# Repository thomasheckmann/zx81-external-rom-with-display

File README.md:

# zx81-external-rom-with-display
ZX81 External ROM interface with partial display logic. The aim of this interface is to be able to run ZX81 ROMS with alternative character set, as found in different Forth ROMS and the ASZMIC rom, without having the need to open up your ZX81 and replace the internal ROM.

Partial display logic only, as this is what's available at the extension bus.

# version 1.0
Board populated with all components. Works great and can even downgrade your ZX81 to a ZX80 :-)

With this interface it is now possible to run ROMs such as the ZX.ASZMIC, Skyware Forth and even the ZX80 ROM.

PLEASE NOTE: The display with this interface will make the ZX81 run as in FAST mode, since there is for now no way to implement the SLOW mode display externally. And one of the main goal is to avoid modifying your existing ZX81.

BOM for v1.0:
- [ ] M28C64 EEPROM (8K eeprom)
- [ ] 74LS157 x 3
- [ ] 74LS193
- [ ] 74LS374
- [ ] Diode 1N4148 x 3
- [ ] Resistor 10K
- [ ] 100nF Ceramic Capacitor x 6

## Planned for v1.1
Only some small changes are planned for v1.1 - mostly the NMI generator fix. When running the ZX80 ROM the NMI generator is not turned off, which means the initial state of the generator is unpredictible. For this reason running the ZX80 not always turns out to work, a few on/off should make it work. A simple fix is to make sure the NMI generator is turned off, by using a few resistors.

Will change the diode from 1N4148 to BAT85, as recommended for this type of usage.

Replace IC socket with ZIF Test socket, as it turns out that I'm swapping out EEPROMs based on needs and usage.

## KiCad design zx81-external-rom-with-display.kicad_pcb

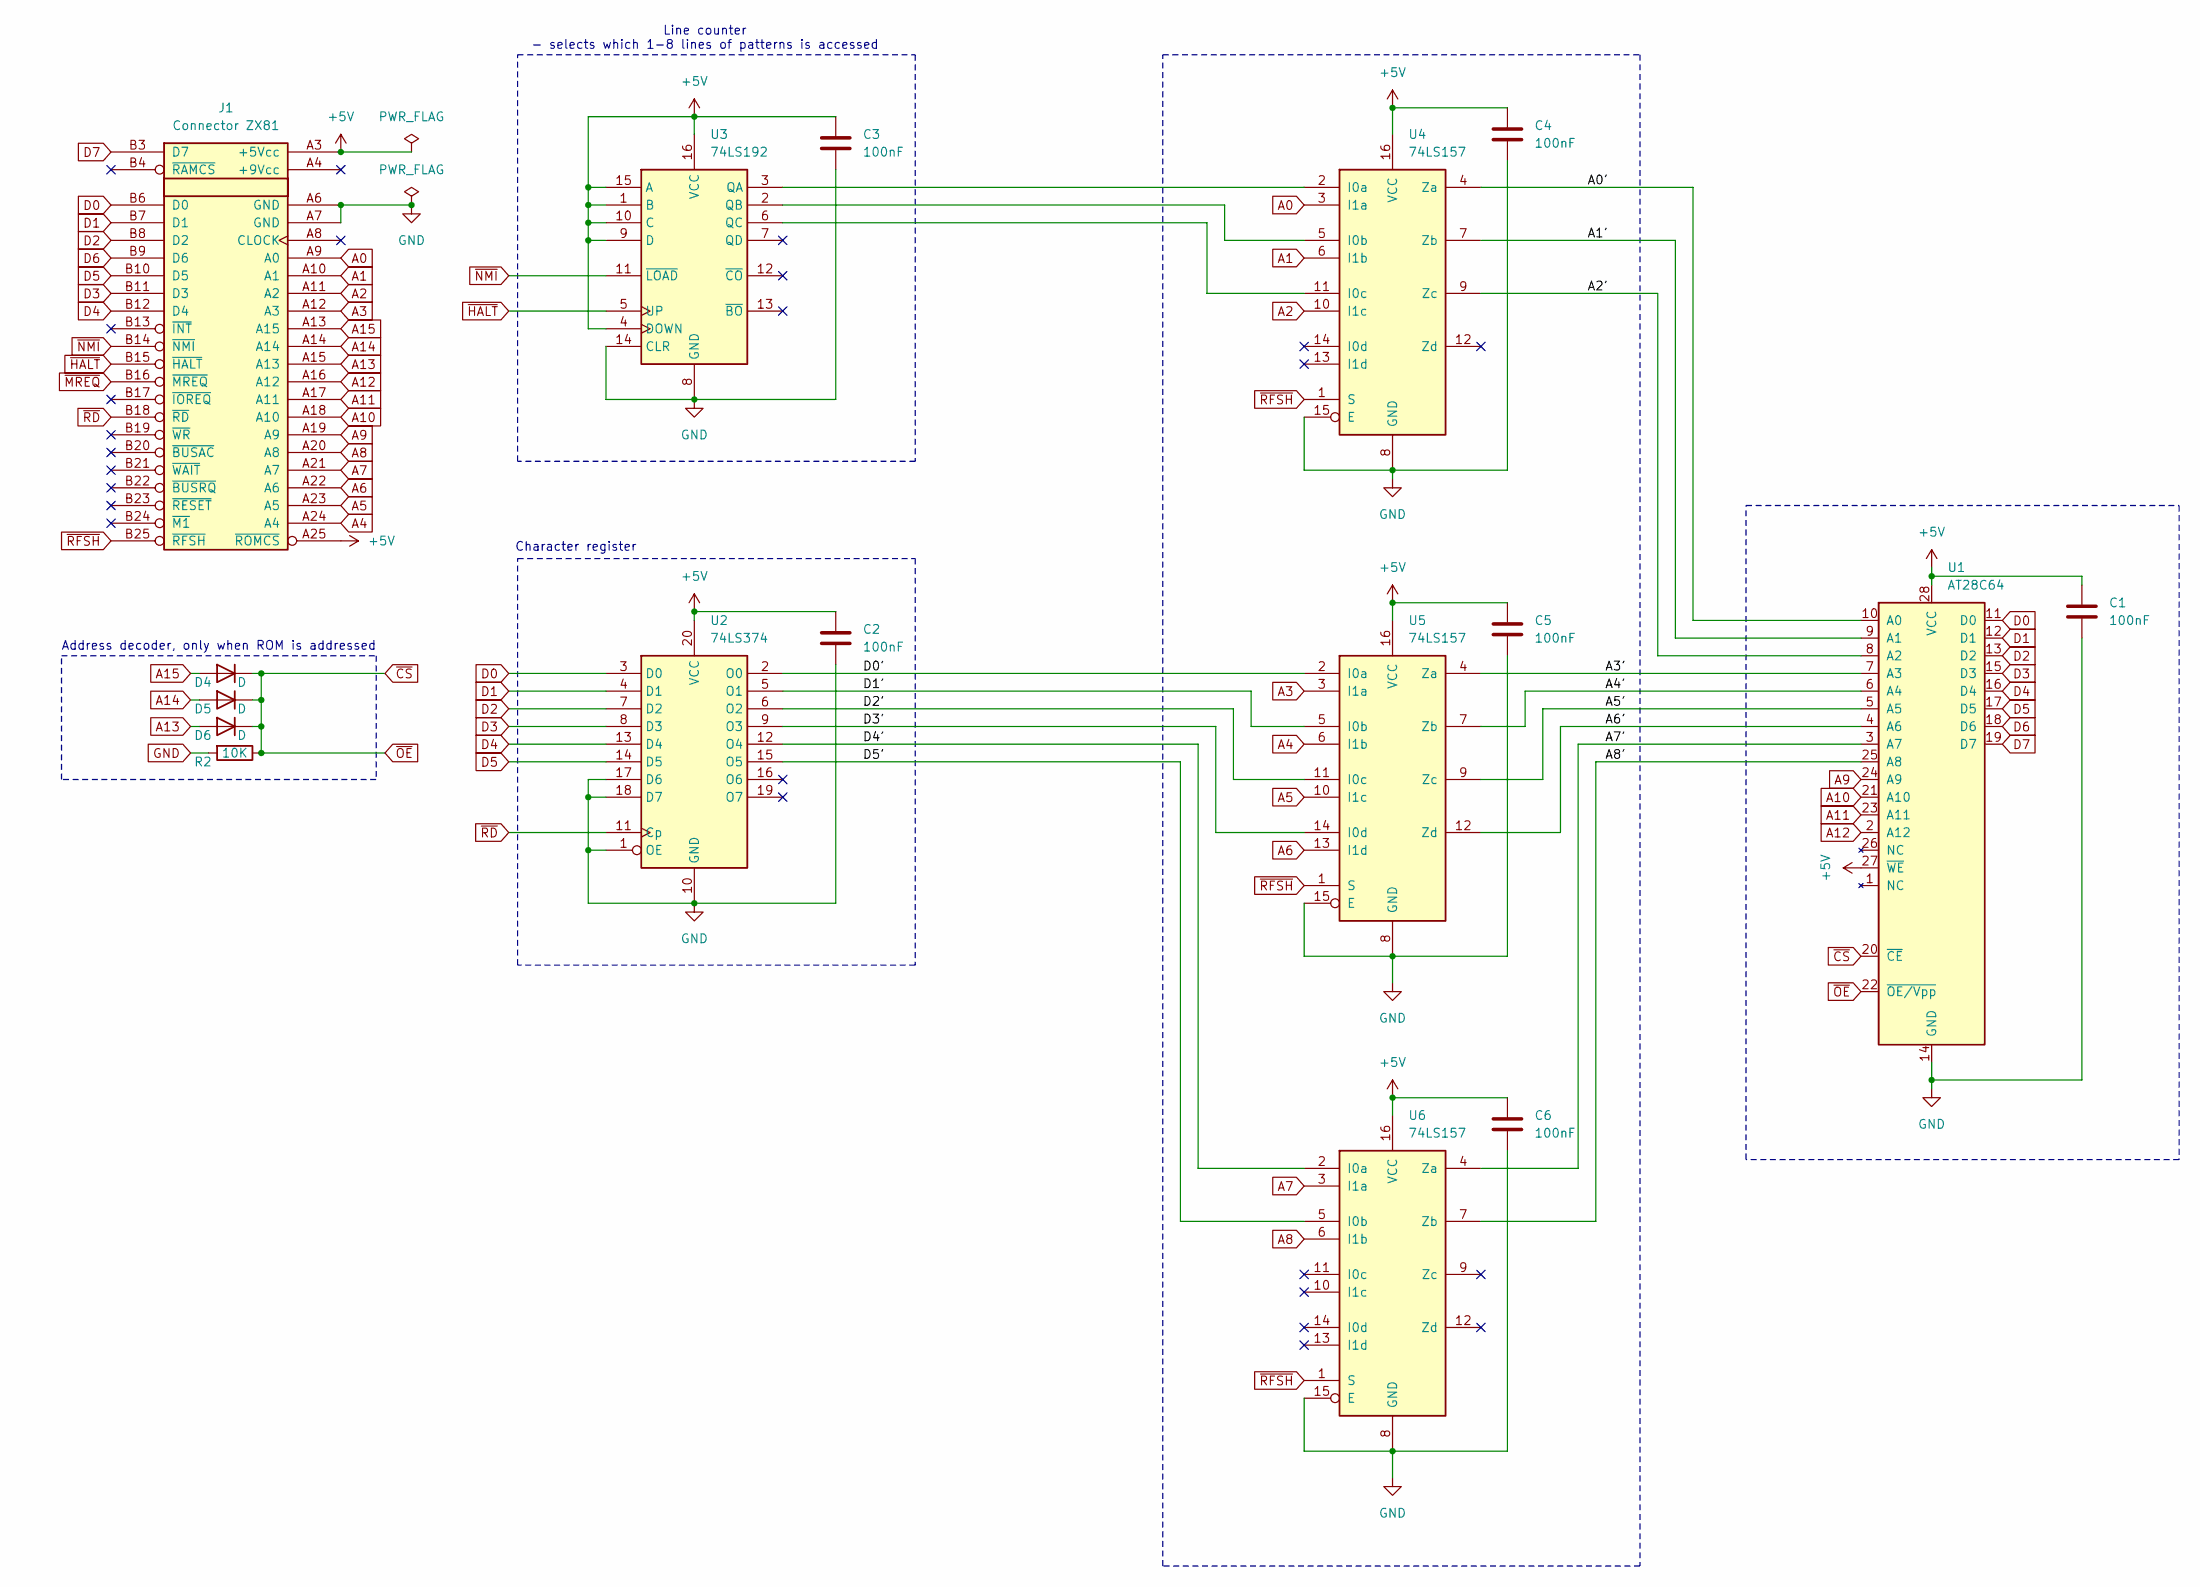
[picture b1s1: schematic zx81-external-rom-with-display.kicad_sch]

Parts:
C1, C2, C3, C4, C5, C6: 100nF; C_Disc_D3.0mm_W1.6mm_P2.50mm
D4, D5, D6: D; D_DO-34_SOD68_P7.62mm_Horizontal
J1: Connector ZX81; EDGE ZX81 BOTTOM
R2: 10K; R_Axial_DIN0204_L3.6mm_D1.6mm_P7.62mm_Horizontal
U1: AT28C64; DIP-28_W15.24mm
U2: 74LS374; DIP-20_W7.62mm
U3: 74LS192; DIP-16_W7.62mm
U4, U5, U6: 74LS157; DIP-16_W7.62mm

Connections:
+5V: C1.1, C2.1, C3.1, C4.1, C5.1, C6.1, J1.A3 (+5Vcc), J1.A25 (~ROMCS), U1.27 (~WE), U1.28 (VCC), U2.20 (VCC), U3.1 (B), U3.4 (DOWN), U3.9 (D), U3.10 (C), U3.15 (A), U3.16 (VCC), U4.16 (VCC), U5.16 (VCC), U6.16 (VCC)
/A0': U1.10 (A0), U4.4 (Za)
/A1': U1.9 (A1), U4.7 (Zb)
/A2': U1.8 (A2), U4.9 (Zc)
/A3': U1.7 (A3), U5.4 (Za)
/A4': U1.6 (A4), U5.7 (Zb)
/A5': U1.5 (A5), U5.9 (Zc)
/A6': U1.4 (A6), U5.12 (Zd)
/A7': U1.3 (A7), U6.4 (Za)
/A8': U1.25 (A8), U6.7 (Zb)
/D0': U2.2 (O0), U5.2 (I0a)
/D1': U2.5 (O1), U5.5 (I0b)
/D2': U2.6 (O2), U5.11 (I0c)
/D3': U2.9 (O3), U5.14 (I0d)
/D4': U2.12 (O4), U6.2 (I0a)
/D5': U2.15 (O5), U6.5 (I0b)
A0: J1.A9 (A0), U4.3 (I1a)
A1: J1.A10 (A1), U4.6 (I1b)
A2: J1.A11 (A2), U4.10 (I1c)
A3: J1.A12 (A3), U5.3 (I1a)
A4: J1.A24 (A4), U5.6 (I1b)
A5: J1.A23 (A5), U5.10 (I1c)
A6: J1.A22 (A6), U5.13 (I1d)
A7: J1.A21 (A7), U6.3 (I1a)
A8: J1.A20 (A8), U6.6 (I1b)
A9: J1.A19 (A9), U1.24 (A9)
A10: J1.A18 (A10), U1.21 (A10)
A11: J1.A17 (A11), U1.23 (A11)
A12: J1.A16 (A12), U1.2 (A12)
A13: D6.2 (A), J1.A15 (A13)
A14: D5.2 (A), J1.A14
A15: D4.2 (A), J1.A13 (A15)
D0: J1.B6 (D0), U1.11 (D0), U2.3 (D0)
D1: J1.B7 (D1), U1.12 (D1), U2.4 (D1)
D2: J1.B8 (D2), U1.13 (D2), U2.7 (D2)
D3: J1.B11 (D3), U1.15 (D3), U2.8 (D3)
D4: J1.B12 (D4), U1.16 (D4), U2.13 (D4)
D5: J1.B10 (D5), U1.17 (D5), U2.14 (D5)
D6: J1.B9 (D6), U1.18 (D6)
D7: J1.B3 (D7), U1.19 (D7)
GND: C1.2, C2.2, C3.2, C4.2, C5.2, C6.2, J1.A6 (GND), J1.A7 (GND), R2.2, U1.14 (GND), U2.1 (OE), U2.10 (GND), U2.17 (D6), U2.18 (D7), U3.8 (GND), U3.14 (CLR), U4.8 (GND), U4.15 (E), U5.8 (GND), U5.15 (E), U6.8 (GND), U6.15 (E)
unnamed: U3.3 (QA), U4.2 (I0a)
unnamed: U3.2 (QB), U4.5 (I0b)
unnamed: U3.6 (QC), U4.11 (I0c)
~CS: D4.1 (K), D5.1 (K), D6.1 (K), R2.1, U1.20 (~CE), U1.22 (~OE/Vpp)
~HALT: J1.B15 (~HALT), U3.5 (UP)
~MREQ: J1.B16 (~MREQ)
~NMI: J1.B14 (~NMI), U3.11 (~LOAD)
~RD: J1.B18 (~RD), U2.11 (Cp)
~RFSH: J1.B25 (~RFSH), U4.1 (S), U5.1 (S), U6.1 (S)

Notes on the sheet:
Line counter - selects which 1-8 lines of patterns is accessed
Address decoder, only when ROM is addressed
Character register

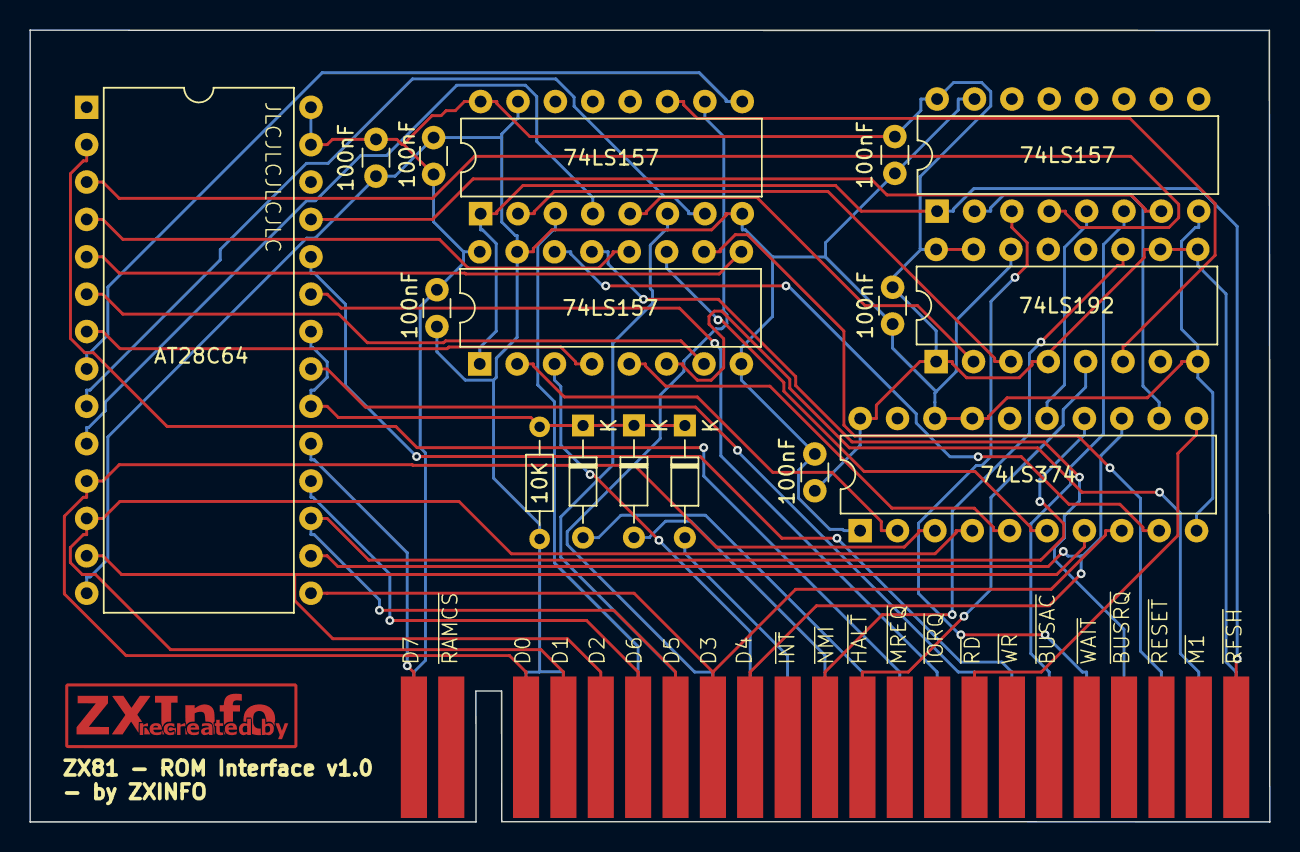
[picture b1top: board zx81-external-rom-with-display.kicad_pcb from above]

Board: 2 copper layers, 84.2 x 53.8 mm, 18 parts (0 on the bottom side), 49 nets.

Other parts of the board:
G200: LOGO; ZXInfo_kicad_logo_copper_16.5x5
